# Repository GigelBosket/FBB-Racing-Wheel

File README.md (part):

# FBB-Racing-Wheel
Custom Racing Wheel with Force Feedback containing the wheelbase and steering wheel with the attachments to connect the 2 together. A custom PCB will be used to control the hoverboard motor and read it's position throw a rotary encoder connected to the motor with 2 gears. A Pico 2 is used in the wheelbase to receive data from the wheel(which also has a pico 2) throw SPI protocol. The pico 2 isn't used only for receiving data from the steering wheel, it could also get data from other devices like pedals, shifter, handrbrake and many more. The pico 2 supports up to 6 SPI/I2C connections and also sensors can directly be connected to it's GPIO pins.

The big difference between my racing wheel and others is that mine has direct data transfer throw the magnetic pins from steering wheel to wheelbase which goes in the pc. That means very small latency and no cable twisting all thanks to the magnetic pins (pogo pins) and the slipring. The downside that comes with this is the plastic parts for the high strain parts like the motor extension and the quick release all from plastic(3d printed) but it still should work fine.

I'm making the project so I could inspire others with my design as it's different than most I've seen. And also it's way cheaper than buying a new one with similar specs.

**Specs:**
 - up to 15nm of torque
 - fast response time of 1ms(1000hz)
 - wheel base is  L=20cm, W=20cm(at the corner, max dist) H=17cm.
 - steering wheel is 33cm
 - the 3d printed case for the steering wheel L=16.2cm, W=3.2cm, H=7.5.
 - 12 buttons
 - 5 encoders
 - 1 funcky switch(for easier customization of the car in games/other actions like camera fix position)
 - high precision encoder(for motor)

Wheel final version below

Wheel base

Close image from the steering wheel face

The back of the steering wheel 

Simple wiring scheme for the Pico 2 of the wheel base to the wires of the slip ring. The image also includes a simple connections from the pico 2 to some sensors if you want to directly connect any sensor to it.

Custom bldc motor driver PCB

PCB image of it's top copper layer

Steering wheel buttons/encoders will be connected to the pico 2 throw a matrix system in which each button is connected to column and row and the pico 2 will send a signal to each column and then wait for output from any of the rows and that's how it will find which buttons got pressed. This matrix system allows the usage of a high number of buttons without haveing a pin for each button. Also a diode will be used to prevent the current from flowing the opposite direction and causing ghosting. The order in which the buttons are connected doesn't matter so I won't include a photo of that. Also I won't add the file for schematic as it's a very simple schematic which isn't linked to other files and it's used to have and idea how the connections work for who doesn't already know(the wires can be connected to others pins and still work fine).Just don't forget to connect it to the pogo pins which then go to the Pico 2 in the wheel base which will process the data, don't forget to wire the pins accordingly for SPI protocol(example above). The pico 2 of the steering wheel is gonna be the slave while the pico in the base is gonna be the master. Slave awaits commands from master.

**Print tips**
So the parts used to connect the motor to the wheel should be printed with 95% infill, the oher parts should be printed with 15-30% infill as they won't have that much strain on them
I m gonna use ASA fillament as it is pretty strong and should do the job well.
Also if you are a total beginer you should download only the stl files as they are the only one needed to print the parts.

I used Raspberry Pi Pico extension in VS code which downloads the SDK for pico and other packages automaticly. If you want to use my code for Pico 2 just git clone my project then open the folder with the code you want to upload on your pico, in VS Code (after installing the extension) and just compile, select port of Pico 2 and upload.

Pico 2:

What you need to wire to the bldc motor driver PCB:

| BOM Total                                 |          |                | Price in us dollars |          |            |                                                                                                                                                                                                                                                                                                                                                                                                                                                                                                                                                                                                                                                                                  |
|-------------------------------------------|----------|----------------|---------------------|----------|------------|----------------------------------------------------------------------------------------------------------------------------------------------------------------------------------------------------------------------------------------------------------------------------------------------------------------------------------------------------------------------------------------------------------------------------------------------------------------------------------------------------------------------------------------------------------------------------------------------------------------------------------------------------------------------------------|
| Material/Product                          | Quantity | Price per Unit | SubTotal            | Shipping | TotalPrice | Link                                                                                                                                                                                                                                                                                                                                                                                                                                                                                                                                                                                                                                                                             |
| HoverBoard Motor                          | 1        | 20             | 20                  | 5        | 25         | Local Market(OLX.ro)                                                                                                                                                                                                                                                                                                                                                                                                                                                                                                                                                                                                                                                             |
| Pico 2                                    | 1        | 5.5            | 5.5                 | 6        | 11.5       | https://www.tme.eu/ro/cart/step/0/order/33780296                                                                                                                                                                                                                                                                                                                                                                                                                                                                                                                                                                                                                                 |
| SK16 support                              | 2        | 5.5            | 11                  | 5        | 16         | https://www.cnc-kit.ro/cumpara/sk16-suport-ax-16-mm-676                                                                                                                                                                                                                                                                                                                                                                                                                                                                                                                                                                                                                          |
| Rotary Encoder 38S6G5-B-G24N              | 1        | 11             | 11                  | 5        | 16         | https://www.aliexpress.com/item/1005006657099269.html?spm=a2g0o.detail.0.0.48bfnCCMnCCMPD&mp=1                                                                                                                                                                                                                                                                                                                                                                                                                                                                                                                                                                                   |
| MicroUsb convertor to Usb A               | 1        | 0.35           | 0.35                | 0        | 0.35       | https://www.aliexpress.com/item/1005005982662099.html?spm=a2g0o.detail.0.0.771aF986F986OE&mp=1                                                                                                                                                                                                                                                                                                                                                                                                                                                                                                                                                                                   |
| Usb C convertor to Usb A                  | 1        | 0.35           | 0.35                | 0        | 0.35       | https://www.aliexpress.com/item/1005005982662099.html?spm=a2g0o.detail.0.0.771aF986F986OE&mp=1                                                                                                                                                                                                                                                                                                                                                                                                                                                                                                                                                                                   |
| Aluminium Profile 20mm x 1m               | 1        | 8              | 8                   | 5        | 13         | https://www.automatic.ro/profiluri-de-aluminiu/510-profil-de-aluminiu-20x20-mm-canal-5-tip-item.html                                                                                                                                                                                                                                                                                                                                                                                                                                                                                                                                                                             |
| M4x10mm Screw                             | 48       | 0.04           | 1.92                | 0        | 1.92       | https://www.dedeman.ro/ro/surub-cu-cap-cilindric-cu-locas-hexagonal-otel-zincat-alb-din-912-8-8-sw-3-m4-x-10-mm/p/1033735                                                                                                                                                                                                                                                                                                                                                                                                                                                                                                                                                        |
| M4 nuts                                   | 48       | 0.012          | 0.576               | 0        | 0.58       | https://www.dedeman.ro/ro/piulita-hexagonala-din-otel-zincat-alb-din-934-m4/p/6000218                                                                                                                                                                                                                                                                                                                                                                                                                                                                                                                                                                                            |
| M5 screw(pack of 5)                       | 1        | 3.62           | 3.62                | 0        | 3.62       | https://www.dedeman.ro/ro/surub-cu-cap-cilindric-cu-locas-hexagonal-otel-zincat-alb-din-912-8-8-m5-x-30-mm-set-5-bucati/p/6014463                                                                                                                                                                                                                                                                                                                                                                                                                                                                                                                                                |
| M5 nuts                                   | 4        | 0.012          | 0.048               | 0        | 0.05       | https://www.dedeman.ro/ro/piulita-hexagonala-din-otel-zincat-alb-din-934-m5/p/6000211                                                                                                                                                                                                                                                                                                                                                                                                                                                                                                                                                                                            |
| Slip Ring                                 | 1        | 14             | 14                  | 0        | 14         | https://www.aliexpress.com/item/1005007469166149.html?spm=a2g0o.tesla.0.0.3dfdCxmRCxmRw3&afTraceInfo=1005007469166149__pc__c_ppc_item_bridge_pc_main__1392mx0__1764524967196                                                                                                                                                                                                                                                                                                                                                                                                                                                                                                     |
| 6 pin magnetic connector(male and female) | 1        | 2              | 2                   | 0        | 2          | https://www.aliexpress.com/item/1005010344872906.html?spm=a2g0o.productlist.0.0.23cd1f3eKvgHZs&mp=1                                                                                                                                                                                                                                                                                                                                                                                                                                                                                                                                                                              |
| Power Supply 24v 20A(80%efficiency)       | 1        | 39             | 39                  | 0        | 39         | https://www.aliexpress.com/item/33051556213.html?spm=a2g0o.cart.0.0.295838daYNvhOv&mp=1                                                                                                                                                                                                                                                                                                                                                                                                                                                                                                                                                                                          |
| 12AWG Red and Black cable                 | 1        | 7              | 7                   | 0        | 7          | https://www.aliexpress.com/item/1005008617874353.html?spm=a2g0o.productlist.main.1.17d020b4Rvij4e&aem_p4p_detail=2025122612534416560488550501840001829804&algo_pvid=f49deaba-5b28-4f73-bf14-0f9abc170d7e&pdp_ext_f=%7B%22order%22%3A%22690%22%2C%22eval%22%3A%221%22%2C%22fromPage%22%3A%22search%22%7D&utparam-url=scene%3Asearch%7Cquery_from%3A%7Cx_object_id%3A1005008617874353%7C_p_origin_prod%3A&search_p4p_id=2025122612534416560488550501840001829804_1                                                                                                                                                                                                                 |
| Steering Wheel                            | 1        | 59             | 59                  | 3        | 62         | https://www.aliexpress.com/item/1005005748732216.html?spm=a2g0o.detail.0.0.771aF986F986OE&mp=1                                                                                                                                                                                                                                                                                                                                                                                                                                                                                                                                                                                   |
| RKJXT1F42001                              | 1        | 3.66           | 3.66                | 0        | 3.66       | https://www.aliexpress.com/item/1005006287472896.html?spm=a2g0o.cart.0.0.295838daYNvhOv&mp=1                                                                                                                                                                                                                                                                                                                                                                                                                                                                                                                                                                                     |
| Push Button                               | 1        | 2.2            | 2.2                 | 0        | 2.2        | https://www.aliexpress.com/item/1005001700262900.html?spm=a2g0o.detail.pcDetailTopMoreOtherSeller.3.dedc2Nkd2Nkdsq&gps-id=pcDetailTopMoreOtherSeller&scm=1007.40050.354490.0&scm_id=1007.40050.354490.0&scm-url=1007.40050.354490.0&pvid=ea68574a-2666-4e59-a2fa-c057ce48ff6b&_t=gps-id:pcDetailTopMoreOtherSeller,scm-url:1007.40050.354490.0,pvid:ea68574a-2666-4e59-a2fa-c057ce48ff6b,tpp_buckets:668%232846%238108%231977&pdp_ext_f=%7B%22order%22%3A%2246%22%2C%22eval%22%3A%221%22%2C%22sceneId%22%3A%2230050%22%2C%22fromPage%22%3A%22recommend%22%7D&utparam-url=scene%3ApcDetailTopMoreOtherSeller%7Cquery_from%3A%7Cx_object_id%3A1005001700262900%7C_p_origin_prod%3A |
| Rotary encoders 15mm shaft(pack of 5)     | 1        | 3.7            | 3.7                 | 0        | 3.7        | https://www.aliexpress.com/item/32877104625.html?spm=a2g0o.productlist.main.1.48556bd7NRqWOd&aem_p4p_detail=202512260523295366502074963100001276967&algo_pvid=1431a988-9934-4868-8815-4e6e2980ab92&pdp_ext_f=%7B%22order%22%3A%229%22%2C%22eval%22%3A%221%22%2C%22fromPage%22%3A%22search%22%7D&utparam-url=scene%3Asearch%7Cquery_from%3A%7Cx_object_id%3A32877104625%7C_p_origin_prod%3A&search_p4p_id=202512260523295366502074963100001276967_1                                                                                                                                                                                                                               |
| Knob of rotary encoders (pack of 10(      | 1        | 1.4            | 1.4                 | 0        | 1.4        | https://www.aliexpress.com/item/1005006995837493.html?spm=a2g0o.productlist.main.16.58eba5a4rt7KPi&algo_pvid=26de8e72-05c5-4207-9564-9d77d845d36d&aem_p4p_detail=2025122605252814300115747411750001318343&pdp_ext_f=%7B%22order%22%3A%222%22%2C%22eval%22%3A%221%22%2C%22fromPage%22%3A%22search%22%7D&utparam-url=scene%3Asearch%7Cquery_from%3A%7Cx_object_id%3A1005006995837493%7C_p_origin_prod%3A&search_p4p_id=2025122605252814300115747411750001318343_6                                                                                                                                                                                                                  |
| M6 x60mm screw                            | 6        | 0.17           | 1.02                | 0        | 1.02       | https://www.dedeman.ro/ro/surub-cu-cap-hexagonal-filetat-complet-otel-zincat-alb-m6-x-60-mm/p/6000728                                                                                                                                                                                                                                                                                                                                                                                                                                                                                                                                                                            |
| M6 nuts                                   | 6        | 0.032          | 0.192               | 0        | 0.19       | https://www.dedeman.ro/ro/piulita-hexagonala-cu-autoblocare-din-otel-din-985-8-m6/p/6006481                                                                                                                                                                                                                                                                                                                                                                                                                                                                                                                                                                                      |
| M3 x16mm screw(pack of 20)                | 1        | 0.86           | 0.86                | 0        | 0.86       | https://www.dedeman.ro/ro/surub-cu-cap-bombat-amprenta-cruce-cu-piulita-easy-fix-otel-zincat-alb-m3-x-16-mm-set-20-bucati/p/6014509                                                                                                                                                                                                                                                                                                                                                                                                                                                                                                                                              |
| 1N4148                                    | 25       | 0.247          | 6.175               | 0        | 6.18       | https://www.tme.eu/ro/details/1n4148-dio/diode-universale-tht/diotec-semiconductor/1n4148/                                                                                                                                                                                                                                                                                                                                                                                                                                                                                                                                                                                       |
| 28AWG Black Cable                         | 2        | 0.5            | 1                   | 0.7      | 1.7        | https://www.aliexpress.com/item/1005008612186010.html?spm=a2g0o.cart.0.0.295838daYNvhOv&mp=1                                                                                                                                                                                                                                                                                                                                                                                                                                                                                                                                                                                     |
| 28AWG Red Cable                           | 2        | 0.5            | 1                   | 0        | 1          | https://www.aliexpress.com/item/1005008612186010.html?spm=a2g0o.cart.0.0.295838daYNvhOv&mp=1                                                                                                                                                                                                                                                                                                                                                                                                                                                                                                                                                                                     |
| PCB(min 5 Q)                              | 1        | 7              | 7                   | 3.12     | 10.12      |                                                                                                                                                                                                                                                                                                                                                                                                                                                                                                                                                                                                                                                                                  |
| PCB BOM(for 1 board)                      | 1        | 32             | 32                  | 9.52     | 41.52      |                                                                                                                                                                                                                                                                                                                                                                                                                                                                                                                                                                                                                                                                                  |
|                                           |          |                |                     |          |            |                                                                                                                                                                                                                                                                                                                                                                                                                                                                                                                                                                                                                                                                                  |
|                                           |          |                |                     |          |            |                                                                                                                                                                                                                                                                                                                                                                                                                                                                                                                                                                                                                                                                                  |
|                                           |          |                | 243.57              | 42.34    | 285.92     |                                                                                                                                                                                                                                                                                                                                                                                                                                                                                                                                              

**PCB BOM**
Price is around 23 euros for parts only on LCSC website + other fees.
| Designator                                                    | Footprint                                      | Quantity | Value                          | LCSC Part # |
|---------------------------------------------------------------|------------------------------------------------|----------|--------------------------------|-------------|
| 50W RESISTOR                                                  | DEGSON DG381-3.5-02P-14-00A(H)                 | 1        | DEGSON DG381-3.5-02P-14-00A(H) | C5272864    |
| C1, C12, C2, C23, C29, C30, C33, C39, C4, C40, C5, C6, C7, C8 | 402                                            | 14       | 100nF                          | C1525       |
| C10, C11, C3, C9                                              | 402                                            | 4        | 4.7uF                          | C23733      |
| C13, C20, C24, C25                                            | 805                                            | 4        | 22uF                           | C711104     |
| C14, C15, C16, C19, C27                                       | 603                                            | 5        | 1uF                            | C15849      |
| C17, C18                                                      | 402                                            | 2        | 15pF                           | C161530     |
| C21, C22, C31, C32, C34                                       | 805                                            | 5        | 10uF                           | C440198     |
| C26                                                           | 603                                            | 1        | 100nF                          | C1591       |
| C28                                                           | 603                                            | 1        | 47nF                           | C1622       |
| C35, C36, C37, C38                                            | CAP_EEEFK1H221P                                | 4        | 220uF                          | C72499      |
| D1                                                            | D_SMC                                          | 1        | SMCJ30A                        | C4154618    |
| D10                                                           | 402                                            | 1        | LED                            | C434446     |
| D2                                                            | D_SMA                                          | 1        | SS14                           | C2837270    |
| J1                                                            | USB_C_Receptacle_G-Switch_GT-USB-7051x         | 1        | USB_C_Receptacle_USB2.0_16P    | C2843970    |
| J3                                                            | JST_SH_BM05B-SRSS-TB_1x05-1MP_P1.00mm_Vertical | 1        | Encoder  Port                  | C160391     |
| J4                                                            | DORABO DB128V-5.08-5P-GN-S                     | 1        | DB128V-5.08-5P-GN-S            | C2927513    |
| L1                                                            | AOTA-B201610S3R3-101-T                         | 1        | 3.3uH                          | C42411119   |
| L2                                                            | VLS6045EX-4R7M-H                               | 1        | 4.7 uH                         | C360735     |
| L3                                                            | IND_ETQP4M220KVK                               | 1        | ETQP4M220KVK                   | C542324     |
| Q1, Q2, Q3, Q4, Q5, Q6                                        | TDSON-8-1                                      | 6        | CSD18532Q5B                    | C882766     |
| Q7                                                            | SOT-23                                         | 1        | IRLZ44N(UMW)                   | C42370423   |
| R1, R5, R6                                                    | 402                                            | 3        | 33                             | C25105      |
| R13, R14, R15, R4, R7                                         | 402                                            | 5        | 1k                             | C11702      |
| R16, R19, R29, R31                                            | 402                                            | 4        | 10k                            | C25744      |
| R18                                                           | 402                                            | 1        | 100k                           | C25741      |
| R2, R3                                                        | 402                                            | 2        | 5k1                            | C25905      |
| R20, R21, R22                                                 | 2512                                           | 3        | 5M1                            | C419720     |
| R30                                                           | 402                                            | 1        | 31k6                           | C11463      |
| R8, R9                                                        | 402                                            | 2        | 27                             | C278580     |
| S1                                                            | SW_TL3365AF180QG                               | 1        | TL3365AF180QG                  | C2886926    |
| U1                                                            | QFN-48-1EP_7x7mm_P0.5mm_EP5.3x5.3mm            | 1        | DRV8323RSRGZR                  | C545497     |
| U2                                                            | QFN-60-1EP_7x7mm_P0.4mm_EP3.4x3.4mm            | 1        | RP2354A                        | C41378174   |
| U3                                                            | TSOT-23-6                                      | 1        | AP63203WU                      | C780769     |
| Y2                                                            | XTAL_ABM8-272-T3                               | 1        | ABM8-272-T3                    | C20625731   |

The next 2 BOMS are an aproximation for how much for just one of them. It is not 100% accurate

|Wheelbase                                |        |              |         |         |Price in US dollars|                                                                                                                                                                                                                                                                                                                                                                                                                                                            |
|-----------------------------------------|--------|--------------|---------|---------|-------------------|----------------------------------------------------------------------------------------------------------------------------------------------------------------------------------------------------------------------------------------------------------------------------------------------------------------------------------------------------------------------------------------------------------------------------------------------------------------|
|Material/Product                         |Quantity|Price per Unit|SubTotal |Shipping |TotalPrice         |Link                                                                                                                                                                                                                                                                                                                                                                                                                                                            |
|HoverBoard Motor                         |1       |20            |20       |5        |25                 |Local Market(OLX.ro)                                                                                                                                                                                                                                                                                                                                                                                                                                                                                                                                                                                                                                                   |
|Pico 2                                   |1       |5.5           |5.5      |6        |11.5               |[link](https://www.tme.eu/ro/cart/step/0/order/33780296)                                                                                                                                                                                                                                                                                                                                                                                                                |
|SK16 support                             |2       |5.5           |11       |5        |16                 |[link](https://www.cnc-kit.ro/cumpara/sk16-suport-ax-16-mm-676)                                                                                                                                                                                                                                                                                                                                                                                                         |
|Rotary Encoder 38S6G5-B-G24N             |1       |11            |11       |5        |16                 |[link](https://www.aliexpress.com/item/1005006657099269.html?spm=a2g0o.detail.0.0.48bfnCCMnCCMPD&mp=1)                                                                                                                                                                                                                                                                                                                                                                  |
|MicroUsb convertor to Usb A              |1       |0.35          |0.35     |0        |0.35               |[link](https://www.aliexpress.com/item/1005005982662099.html?spm=a2g0o.detail.0.0.771aF986F986OE&mp=1)                                                                                                                                                                                                                                                                                                                                                                  |
|Usb C convertor to Usb A                 |1       |0.35          |0.35     |0        |0.35               |[link](https://www.aliexpress.com/item/1005005982662099.html?spm=a2g0o.detail.0.0.771aF986F986OE&mp=1)                                                                                                                                                                                                                                                                                                                                                                  |
|Aluminium Profile 20mm x 1m              |1       |8             |8        |5        |13                 |[link](https://www.automatic.ro/profiluri-de-aluminiu/510-profil-de-aluminiu-20x20-mm-canal-5-tip-item.html)                                                                                                                                                                                                                                                                                                                                                            |
|M4x10mm Screw                            |48      |0.04          |1.92     |0        |1.92               |[link](https://www.dedeman.ro/ro/surub-cu-cap-cilindric-cu-locas-hexagonal-otel-zincat-alb-din-912-8-8-sw-3-m4-x-10-mm/p/1033735)                                                                                                                                                                                                                                                                                                                                       |
|M4 nuts                                  |48      |0.012         |0.576    |0        |0.58               |[link](https://www.dedeman.ro/ro/piulita-hexagonala-din-otel-zincat-alb-din-934-m4/p/6000218)                                                                                                                                                                                                                                                                                                                                                                           |                                                                                                                                                                                                                                                                                                                                                                                                                                                               |
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
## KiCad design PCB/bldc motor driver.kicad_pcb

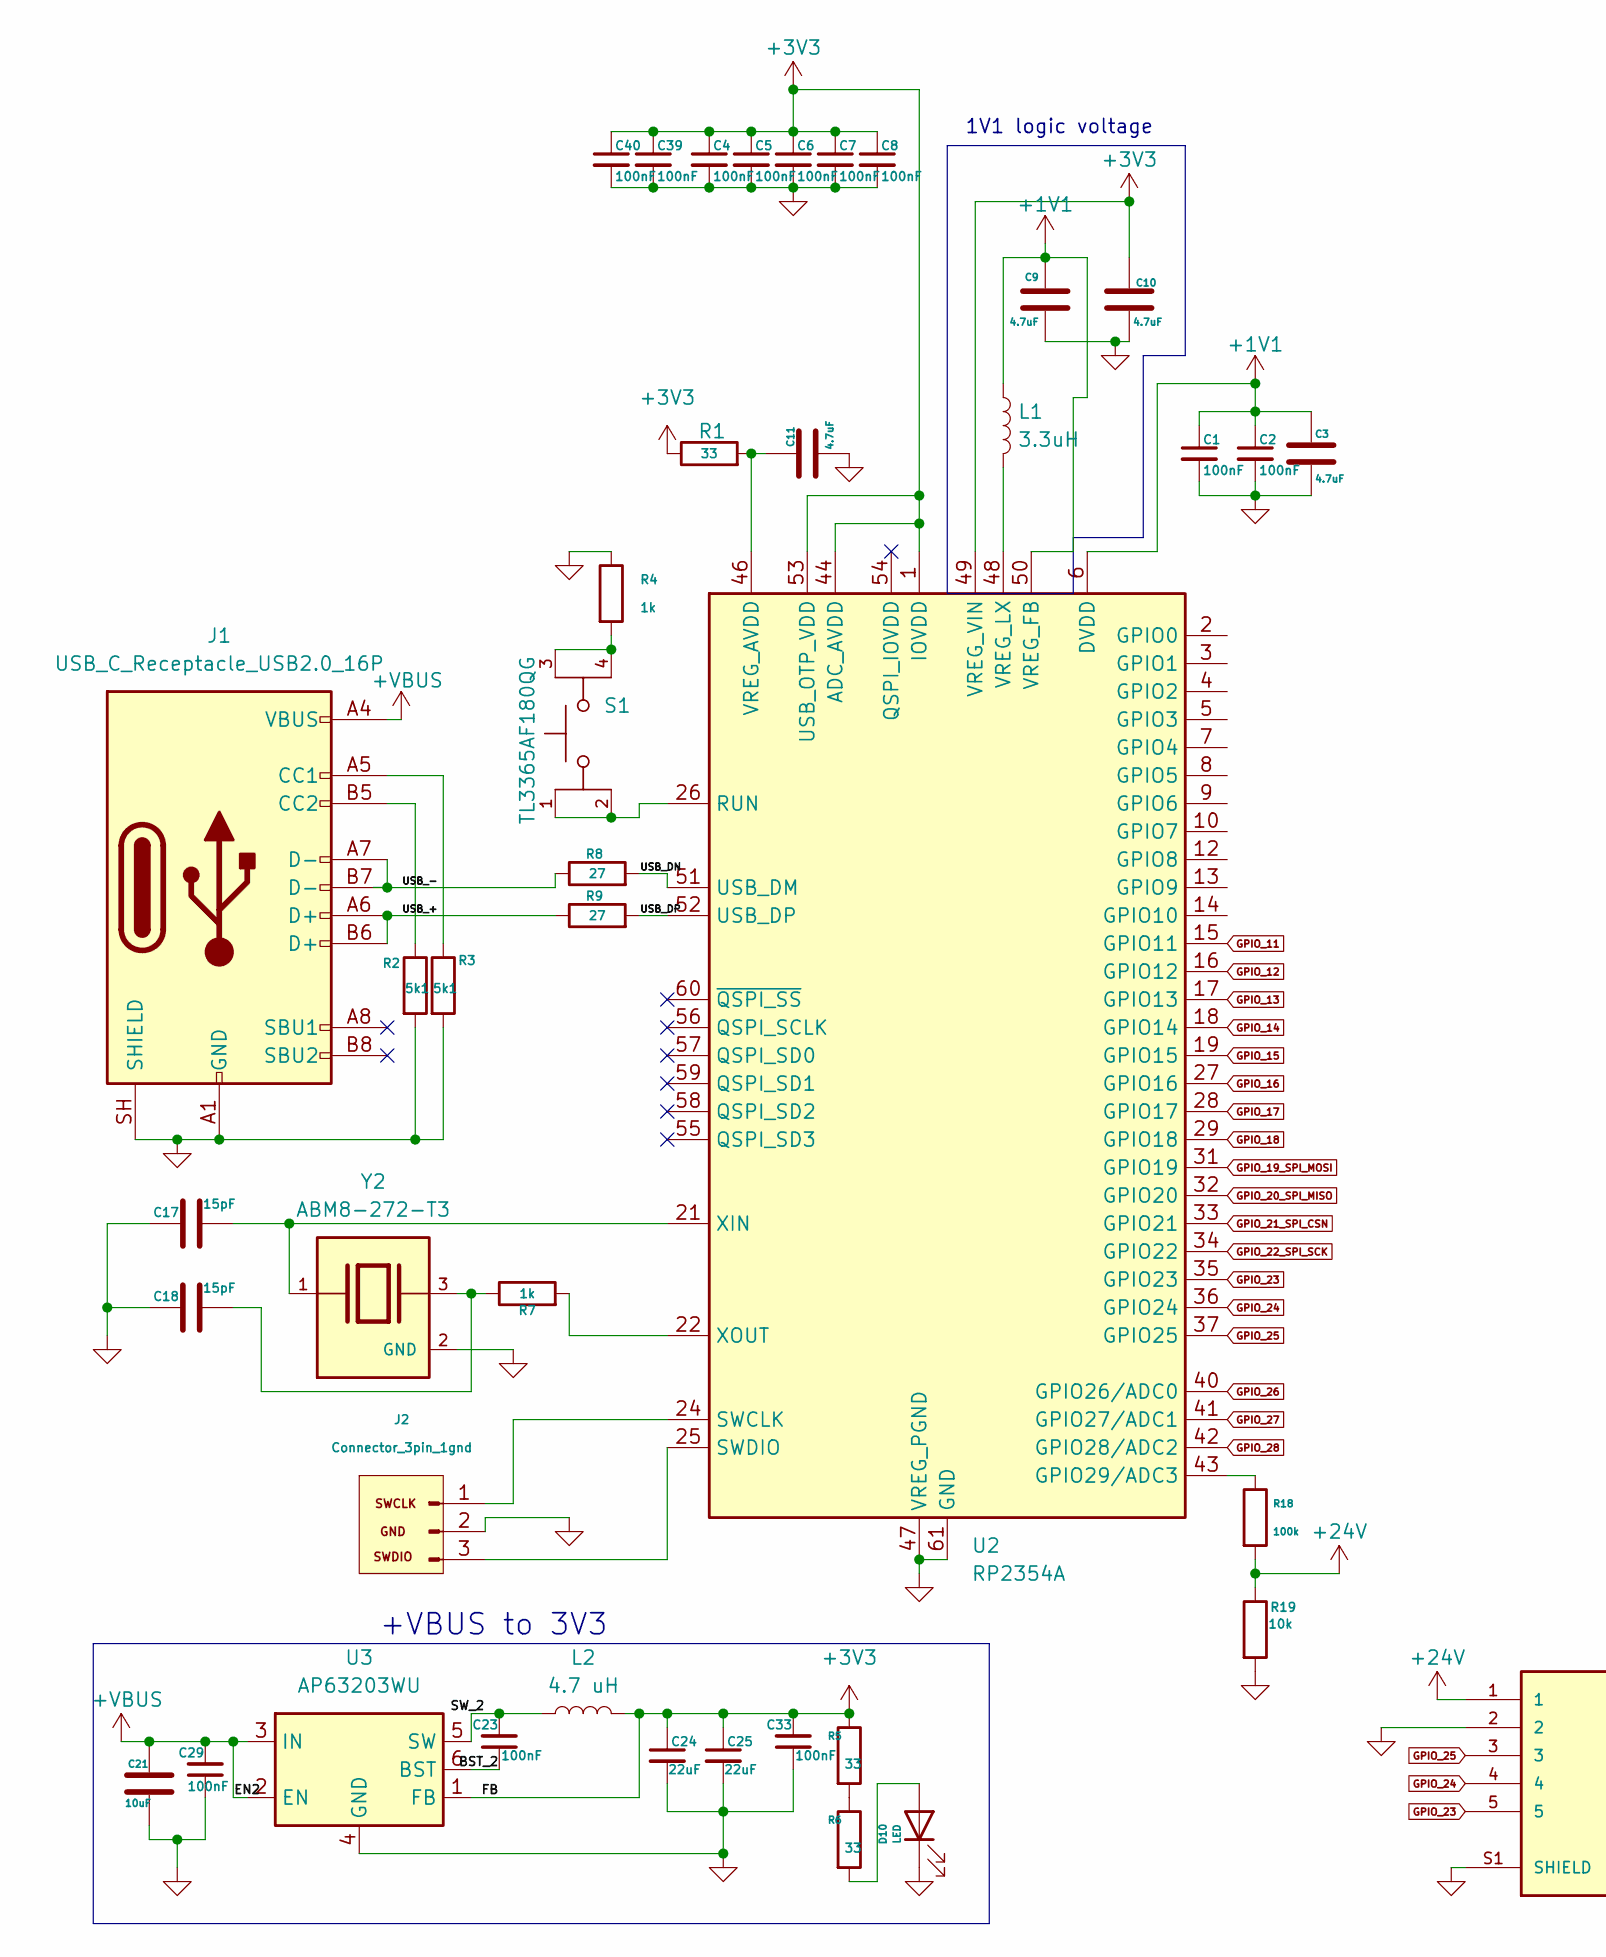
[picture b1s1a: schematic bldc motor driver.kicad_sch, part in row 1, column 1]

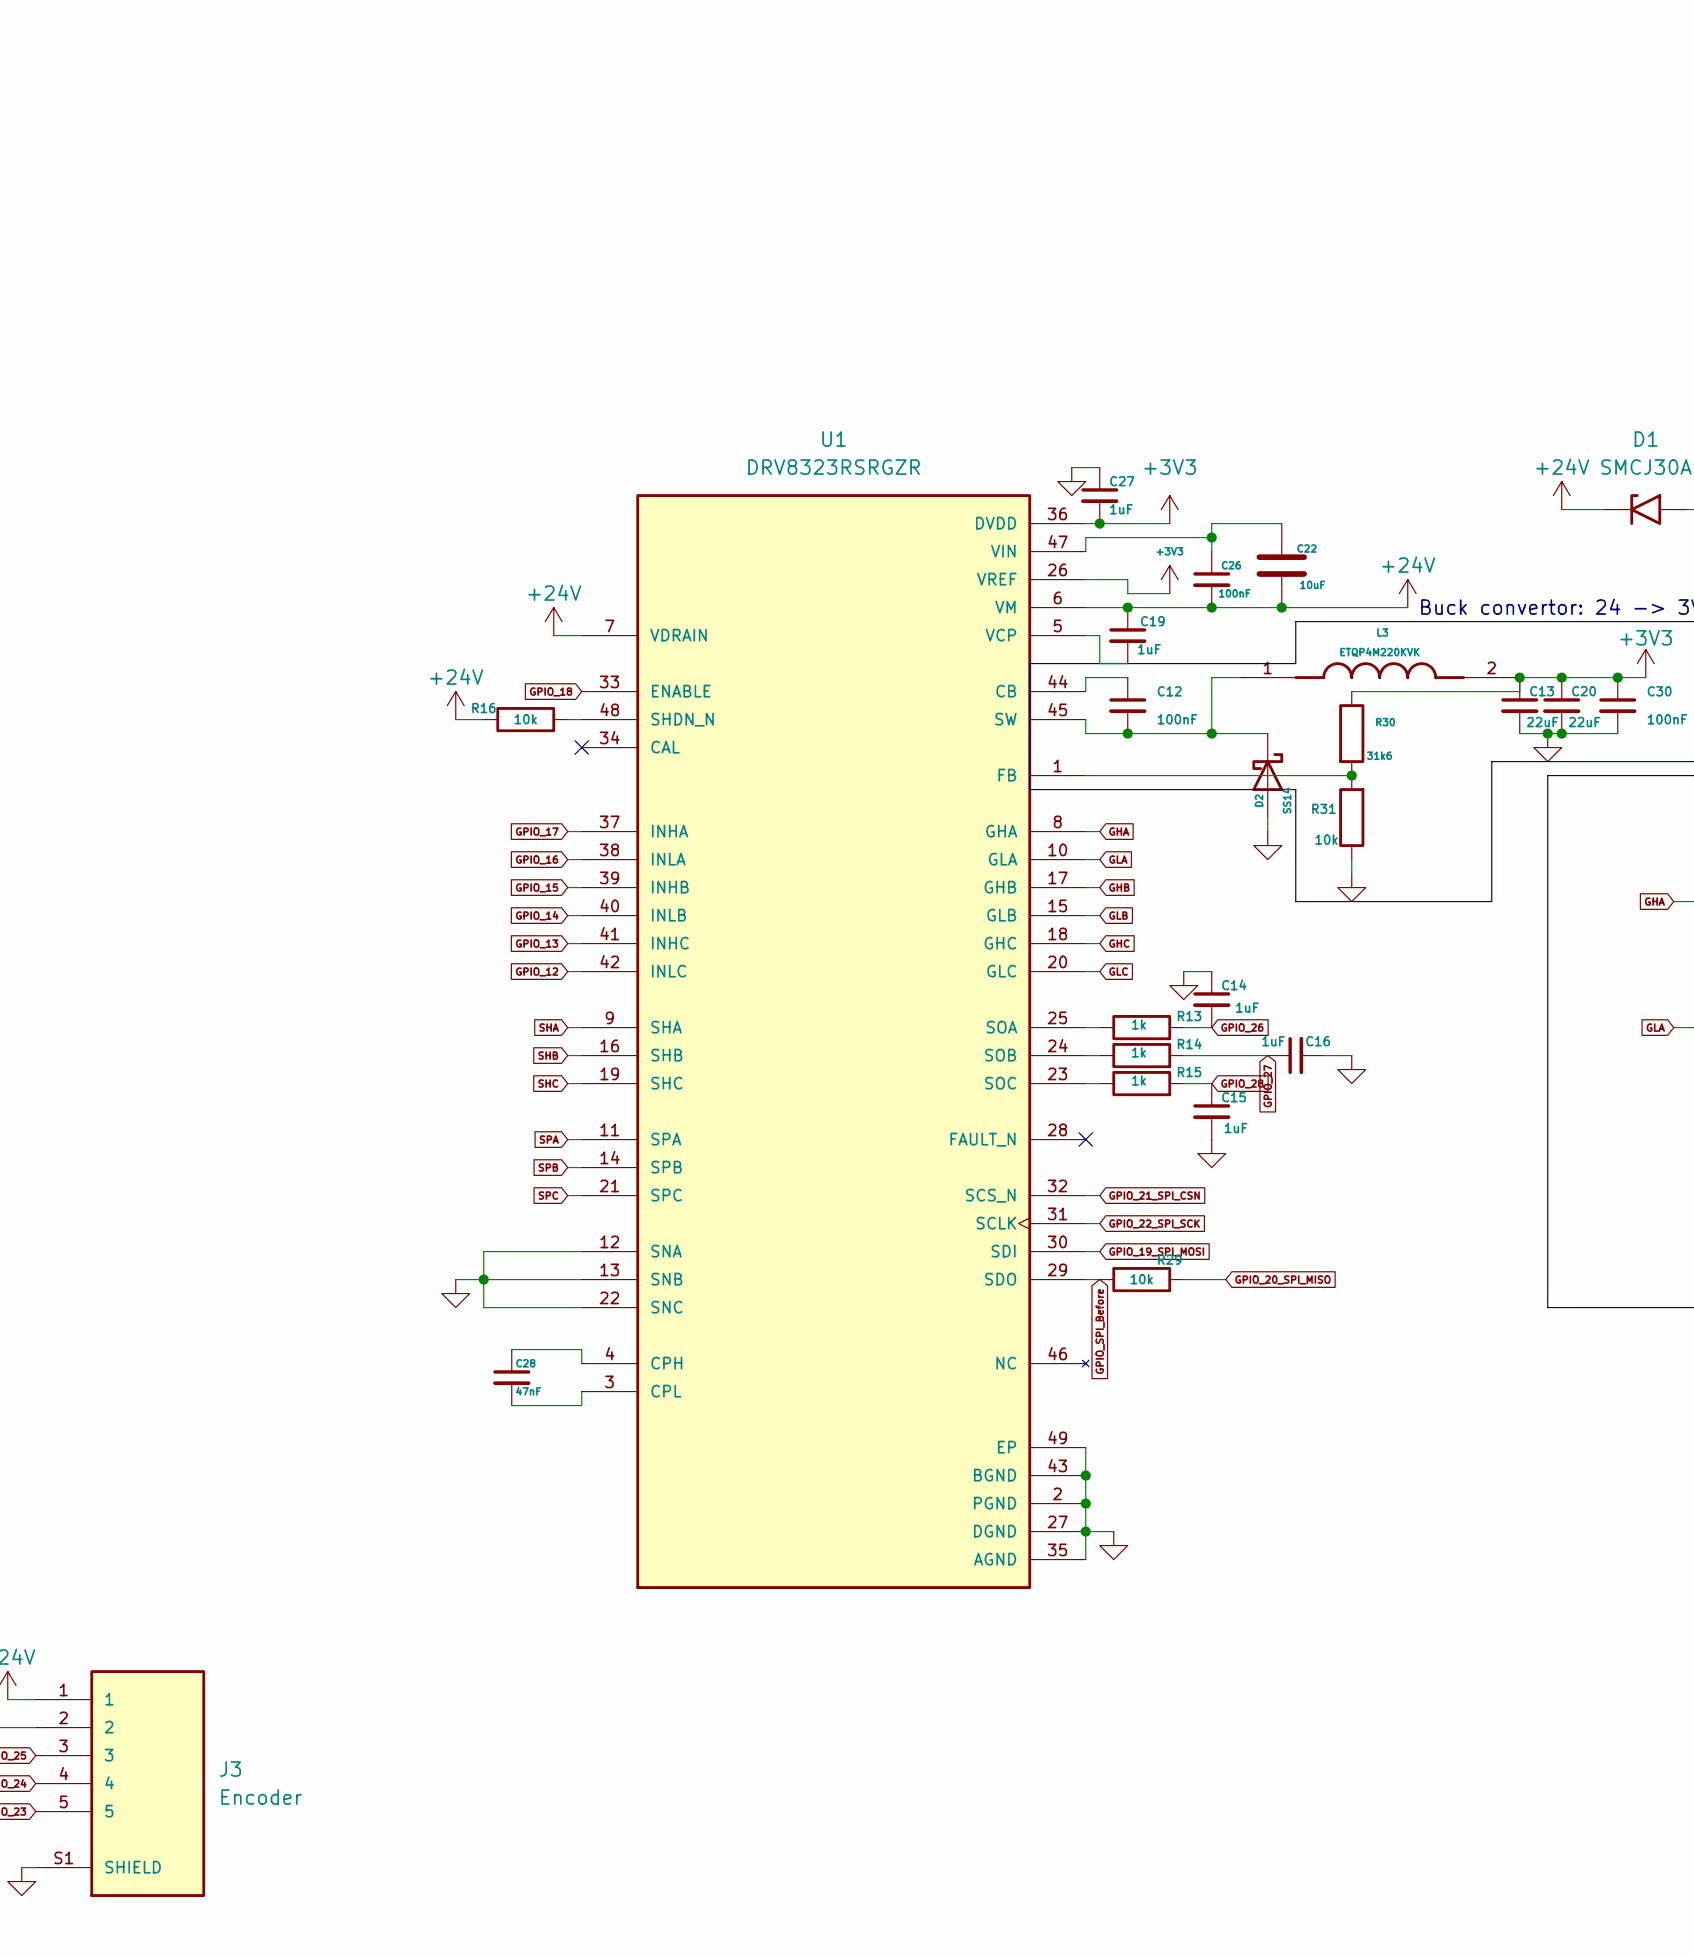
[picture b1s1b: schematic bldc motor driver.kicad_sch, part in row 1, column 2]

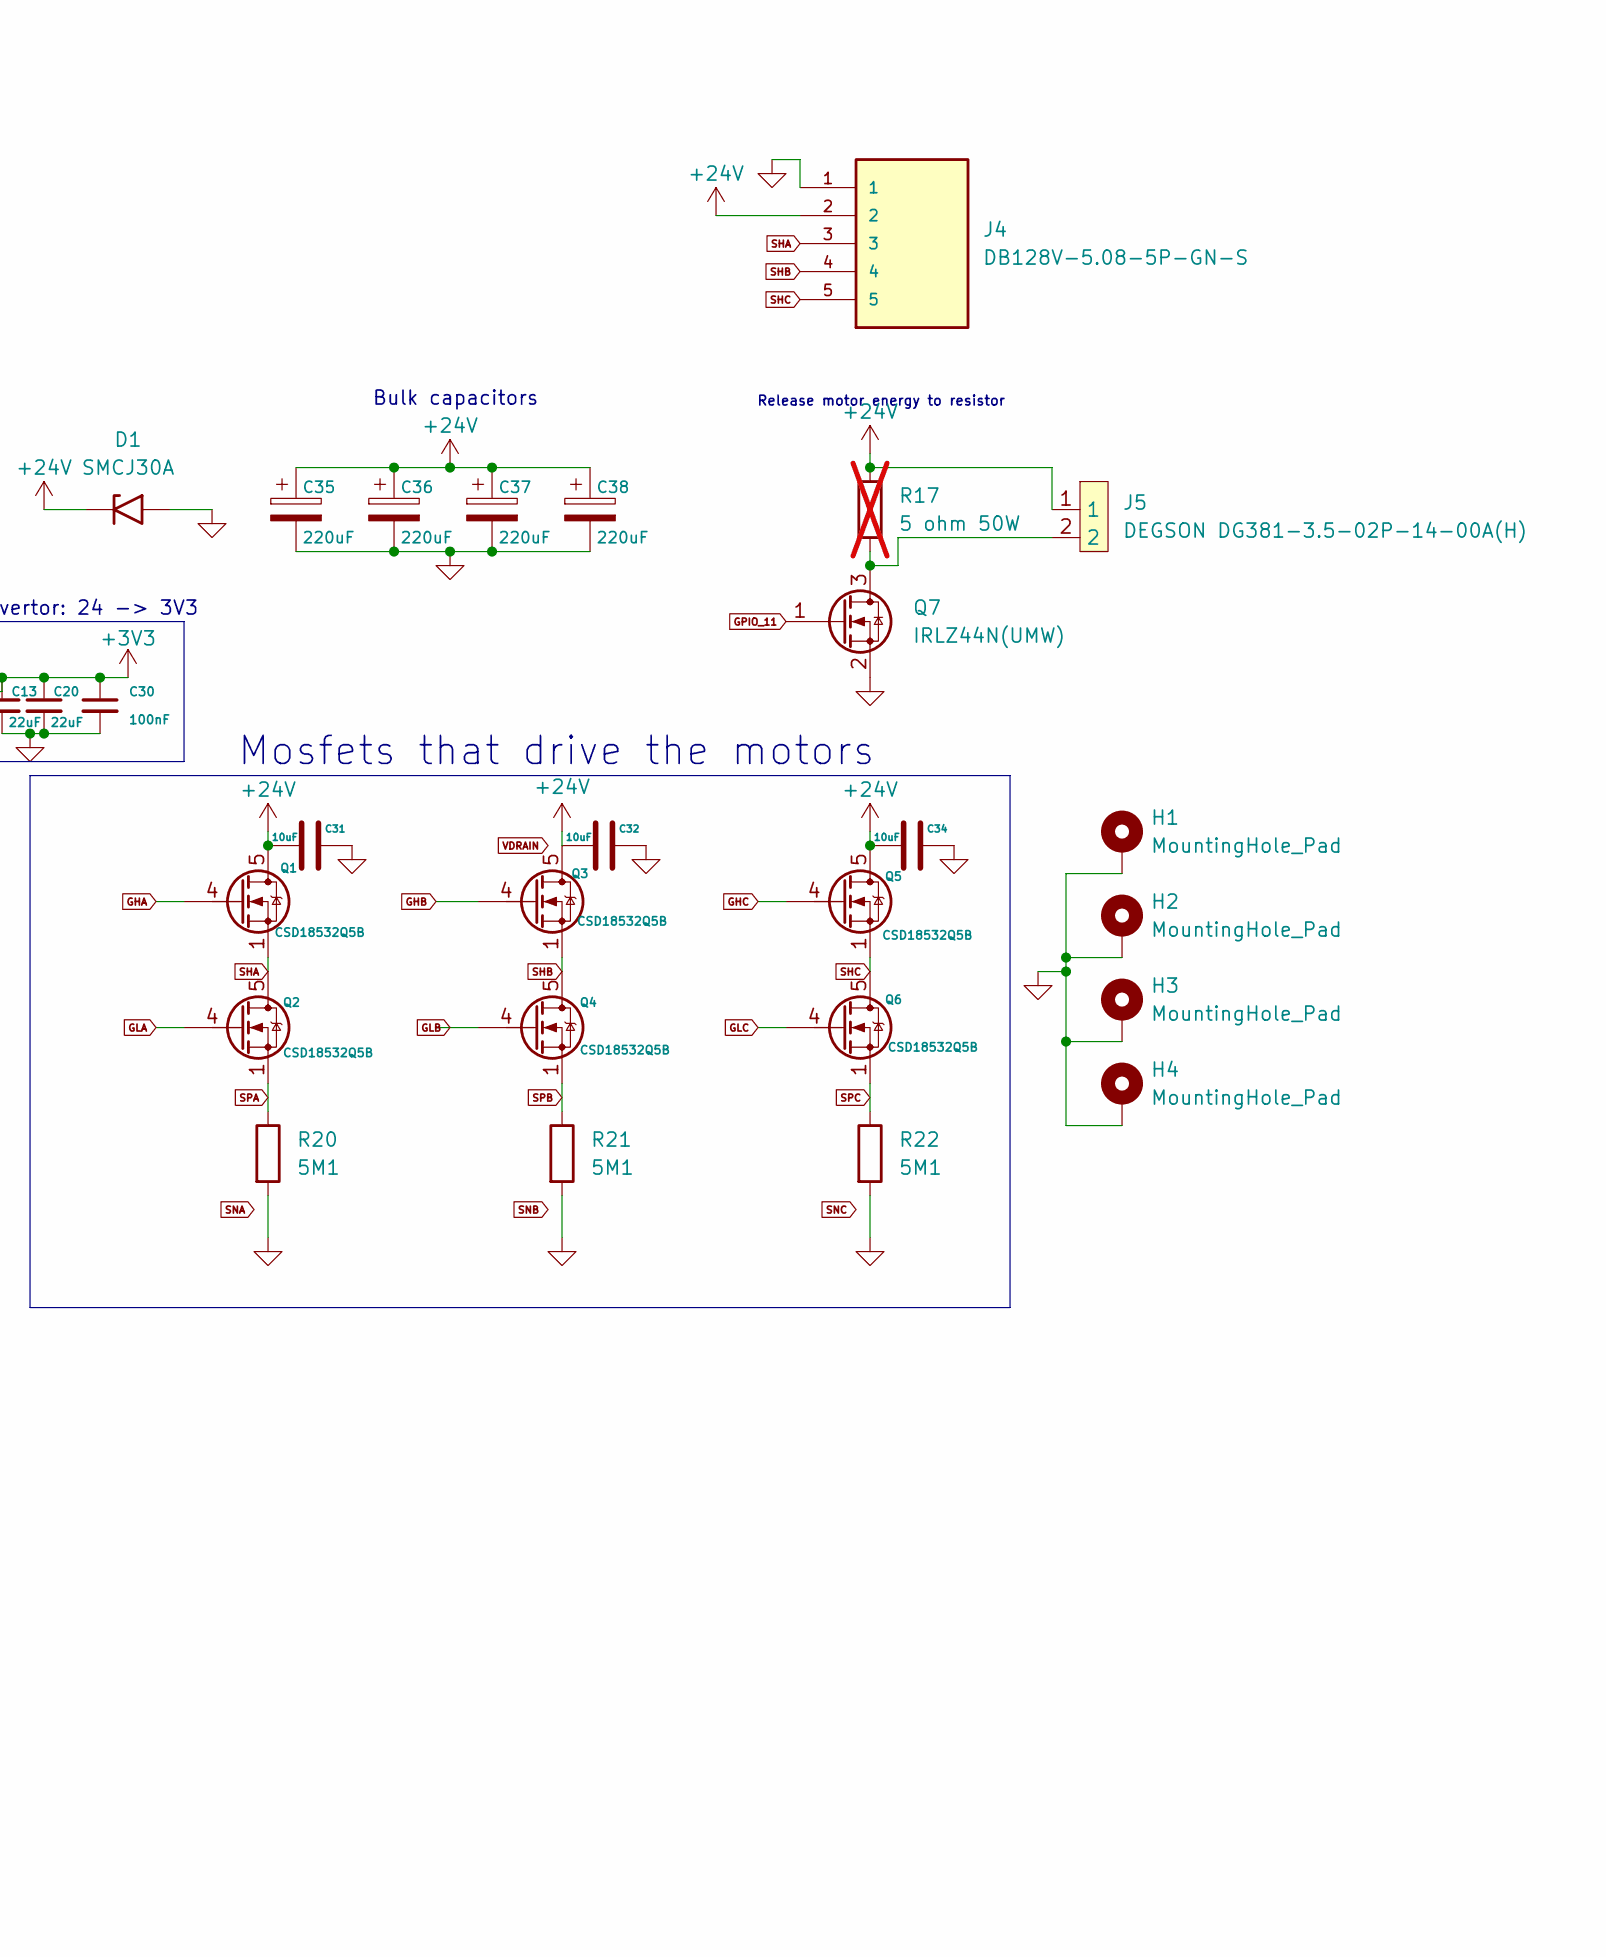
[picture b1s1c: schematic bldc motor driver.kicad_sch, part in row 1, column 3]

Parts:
C1, C2, C4, C5, C6, C7, C8, C12, C30, C39, C40: 100nF; C_0402_1005Metric; MPN CL05B104KO5NNNC; LCSC C1525
C3, C9, C10, C11: 4.7uF; C_0402_1005Metric; MPN CL05A475MP5NRNC; LCSC C23733
C13, C20, C24, C25: 22uF; C_0805_2012Metric; MPN GXT21BR61C226ME13L; LCSC C711104
C14, C15, C16, C19, C27: 1uF; C_0603_1608Metric; MPN CL10A105KB8NNNC; LCSC C15849
C17, C18: 15pF; C_0402_1005Metric smaller silk; MPN GRM1555C1H150FA01D; LCSC C161530
C21, C22, C31, C32, C34: 10uF; C_0805_2012Metric; MPN GRM21BR61H106KE43L; LCSC C440198
C23, C29, C33: 100nF; C_0402_1005Metric smaller silk; MPN CL05B104KO5NNNC; LCSC C1525
C26: 100nF; C_0603_1608Metric; MPN CL10B104KB8NNNC; LCSC C1591
C28: 47nF; C_0603_1608Metric; MPN CL10B473KB8NNNC; LCSC C1622
C35, C36, C37, C38: 220uF; CAP_EEEFK1H221P; MPN RVT1H221M1010; LCSC C72499
D1: SMCJ30A; D_SMC; MPN SMCJ30A; LCSC C4154618
D2: SS14; D_SMA; MPN SS14; LCSC C2837270
D10: LED; LED_0402_1005Metric; MPN SZYY0402G; LCSC C434446
H1, H2, H3, H4: MountingHole_Pad; MountingHole_2.2mm_M2_DIN965_Pad
J1: USB_C_Receptacle_USB2.0_16P; USB_C_Receptacle_G-Switch_GT-USB-7051x
J2: Connector_3pin_1gnd; 3 pin connector middle ground
J3: Encoder; JST_SH_BM05B-SRSS-TB_1x05-1MP_P1.00mm_Vertical; PARTREV N/A
J4: DB128V-5.08-5P-GN-S; DORABO DB128V-5.08-5P-GN-S; MPN DB128V-5.08-5P-GN-S; LCSC C2927513
J5: DEGSON DG381-3.5-02P-14-00A(H); MPN DG381-3.5-02P-14-00A(H); LCSC C5272864
L1: 3.3uH; AOTA-B201610S3R3-101-T; MPN AOTA-B201610S3R3-101-T; LCSC C42411119
L2: 4.7 uH; VLS6045EX-4R7M-H; MPN VLS6045EX-4R7M-H; LCSC C360735
L3: ETQP4M220KVK; IND_ETQP4M220KVK; PARTREV 1-Feb-20; LCSC C542324
Q1, Q2, Q3, Q4, Q5, Q6: CSD18532Q5B; TDSON-8-1
Q7: IRLZ44N(UMW); SOT-23; MPN IRLZ44N(UMW); LCSC C42370423
R1, R5, R6: 33; R_0402_1005Metric; MPN 0402WGF330JTCE; LCSC C25105
R2, R3: 5k1; R_0402_1005Metric smaller silkscreen; MPN 0402WGF5101TCE; LCSC C25905
R4, R13, R14, R15: 1k; R_0402_1005Metric; MPN 0402WGF1001TCE; LCSC C11702
R7: 1k; R_0402_1005Metric smaller silkscreen; MPN 0402WGF1001TCE; LCSC C11702
R8, R9: 27; R_0402_1005Metric; MPN ERJ-2GEJ270X; LCSC C278580
R16, R19, R29, R31: 10k; R_0402_1005Metric smaller silkscreen; MPN 0402WGF1002TCE; LCSC C25744
R17: 5 ohm 50W; MPN HoRX-50W-5R-5%; LCSC C2923747; not fitted
R18: 100k; R_0402_1005Metric; MPN 0402WGF1003TCE; LCSC C25741
R20, R21, R22: 5M1; R_2512_6332Metric; MPN 25121WJ0515T4E; LCSC C419720
R30: 31k6; R_0402_1005Metric; MPN 0402WGF3162TCE; LCSC C11463
S1: TL3365AF180QG; SW_TL3365AF180QG; PARTREV A
U1: DRV8323RSRGZR; QFN-48-1EP_7x7mm_P0.5mm_EP5.3x5.3mm; PARTREV C
U2: RP2354A; QFN-60-1EP_7x7mm_P0.4mm_EP3.4x3.4mm
U3: AP63203WU; TSOT-23-6; MPN AP63203WU-7; LCSC C780769
Y2: ABM8-272-T3; XTAL_ABM8-272-T3; PARTREV 07-29-20; LCSC C20625731

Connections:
+1V1: C1.1, C2.1, C3.1, C9.1, L1.1, U2.6 (DVDD), U2.23 (DVDD), U2.39 (DVDD), U2.50 (VREG_FB)
+3V3: C4.1, C5.1, C6.1, C7.1, C8.1, C10.1, C13.1, C20.1, C24.1, C25.1, C27.2, C30.1, C33.2, C39.1, C40.1, L2.2, L3.2, R1.1, R5.1, R30.1, U1.26 (VREF), U1.36 (DVDD), U2.1 (IOVDD), U2.11 (IOVDD), U2.20 (IOVDD), U2.30 (IOVDD), U2.38 (IOVDD), U2.44 (ADC_AVDD), U2.45 (IOVDD), U2.49 (VREG_VIN), U2.53 (USB_OTP_VDD), U3.1 (FB)
+24V: C19.1, C22.2, C26.2, C31.1, C32.1, C34.1, C35.1, C36.1, C37.1, C38.1, D1.1 (A1), J3.1, J4.2, J5.1, Q1.5 (D), Q3.5 (D), Q5.5 (D), R16.1, R17.1, R18.2, R19.1, U1.6 (VM), U1.7 (VDRAIN); also elsewhere on the board
+VBUS: C21.1, C29.2, J1.A4 (VBUS), J1.A9 (VBUS), J1.B4 (VBUS), J1.B9 (VBUS), U3.2 (EN), U3.3 (IN)
/BST_2: C23.1, U3.6 (BST)
/SW_2: C23.2, L2.1, U3.5 (SW)
/USB_+: J1.A6 (D+), J1.B6 (D+), R9.1
/USB_-: J1.A7 (D-), J1.B7 (D-), R8.1
/USB_DN: R8.2, U2.51 (USB_DM)
/USB_DP: R9.2, U2.52 (USB_DP)
GHA: Q1.4 (G), U1.8 (GHA)
GHB: Q3.4 (G), U1.17 (GHB)
GHC: Q5.4 (G), U1.18 (GHC)
GLA: Q2.4 (G), U1.10 (GLA)
GLB: Q4.4 (G), U1.15 (GLB)
GLC: Q6.4 (G), U1.20 (GLC)
GND: C1.2, C2.2, C3.2, C4.2, C5.2, C6.2, C7.2, C8.2, C9.2, C10.2, C11.2, C13.2, C14.1, C15.2, C16.2, C17.1, C18.1, C20.2, C21.2, C24.2, C25.2, C27.1, C29.1, C30.2, C31.2, C32.2, C33.1, C34.2, C35.2, C36.2, C37.2, C38.2, C39.2, C40.2, D1.2 (A2), D2.2 (A), D10.1 (K), H1.1 (1_1), H2.1 (1_1), H3.1 (1_1), H4.1 (1_1), J1.A1 (GND), J1.A12 (GND), J1.B1 (GND), J1.B12 (GND), J1.SH (SHIELD), J2.2 (GND), J3.2, J3.S1 (SHIELD), J3.S2 (SHIELD), J4.1, Q7.2 (S), R2.2, R3.2, R4.1, R19.2, R20.2, R21.2, R22.2, R31.1, U1.2 (PGND), U1.12 (SNA), U1.13 (SNB), U1.22 (SNC), U1.27 (DGND), U1.35 (AGND), U1.43 (BGND), U1.49 (EP), U2.47 (VREG_PGND), U2.61 (GND), U3.4 (GND), Y2.2 (GND), Y2.4 (GND)
GPIO_11: Q7.1 (G), U2.15 (GPIO11)
GPIO_12: U1.42 (INLC), U2.16 (GPIO12)
GPIO_13: U1.41 (INHC), U2.17 (GPIO13)
GPIO_14: U1.40 (INLB), U2.18 (GPIO14)
GPIO_15: U1.39 (INHB), U2.19 (GPIO15)
GPIO_16: U1.38 (INLA), U2.27 (GPIO16)
GPIO_17: U1.37 (INHA), U2.28 (GPIO17)
GPIO_18: U1.33 (ENABLE), U2.29 (GPIO18)
GPIO_19_SPI_MOSI: U1.30 (SDI), U2.31 (GPIO19)
GPIO_20_SPI_MISO: R29.2, U2.32 (GPIO20)
GPIO_21_SPI_CSN: U1.32 (SCS_N), U2.33 (GPIO21)
GPIO_22_SPI_SCK: U1.31 (SCLK), U2.34 (GPIO22)
GPIO_23: J3.5, U2.35 (GPIO23)
GPIO_24: J3.4, U2.36 (GPIO24)
GPIO_25: J3.3, U2.37 (GPIO25)
GPIO_26: C14.2, R13.2, U2.40 (GPIO26/ADC0)
GPIO_27: C16.1, R14.2, U2.41 (GPIO27/ADC1)
GPIO_28: C15.1, R15.2, U2.42 (GPIO28/ADC2)
GPIO_SPI_Before: R29.1, U1.29 (SDO)
unnamed: C18.2, R7.1, Y2.3
unnamed: C12.2, D2.1 (K), L3.1, U1.45 (SW)
unnamed: D10.2 (A), R6.2
unnamed: J1.A5 (CC1), R3.1
unnamed: J1.B5 (CC2), R2.1
unnamed: J2.1 (SWCLK), U2.24 (SWCLK)
unnamed: J2.3 (SWDIO), U2.25 (SWDIO)
unnamed 43: J5.2, Q7.3 (D), R17.2; also elsewhere on the board
unnamed: R4.2, S1.3, S1.4
unnamed: R5.2, R6.1
unnamed: C12.1, U1.44 (CB)
unnamed: C28.1, U1.4 (CPH)
unnamed: C28.2, U1.3 (CPL)
unnamed: R30.2, R31.2, U1.1 (FB)
unnamed: R16.2, U1.48 (SHDN_N)
unnamed: R13.1, U1.25 (SOA)
unnamed: R14.1, U1.24 (SOB)
unnamed: R15.1, U1.23 (SOC)
unnamed: C19.2, U1.5 (VCP)
unnamed: C22.1, C26.1, U1.47 (VIN)
unnamed: R18.1, U2.43 (GPIO29/ADC3)
unnamed: S1.1, S1.2, U2.26 (RUN)
unnamed: C11.1, R1.2, U2.46 (VREG_AVDD)
unnamed: L1.2, U2.48 (VREG_LX)
unnamed: C17.2, U2.21 (XIN), Y2.1
unnamed: R7.2, U2.22 (XOUT)
SHA: J4.3, Q1.1 (S), Q1.2 (S), Q1.3 (S), Q2.5 (D), U1.9 (SHA)
SHB: J4.4, Q3.1 (S), Q3.2 (S), Q3.3 (S), Q4.5 (D), U1.16 (SHB)
SHC: J4.5, Q5.1 (S), Q5.2 (S), Q5.3 (S), Q6.5 (D), U1.19 (SHC)
SPA: Q2.1 (S), Q2.2 (S), Q2.3 (S), R20.1, U1.11 (SPA)
SPB: Q4.1 (S), Q4.2 (S), Q4.3 (S), R21.1, U1.14 (SPB)
SPC: Q6.1 (S), Q6.2 (S), Q6.3 (S), R22.1, U1.21 (SPC)

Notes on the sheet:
Bulk capacitors
+VBUS to 3V3
Release motor energy to resistor
Mosfets that drive the motors
Buck convertor: 24 -> 3V3
1V1 logic voltage

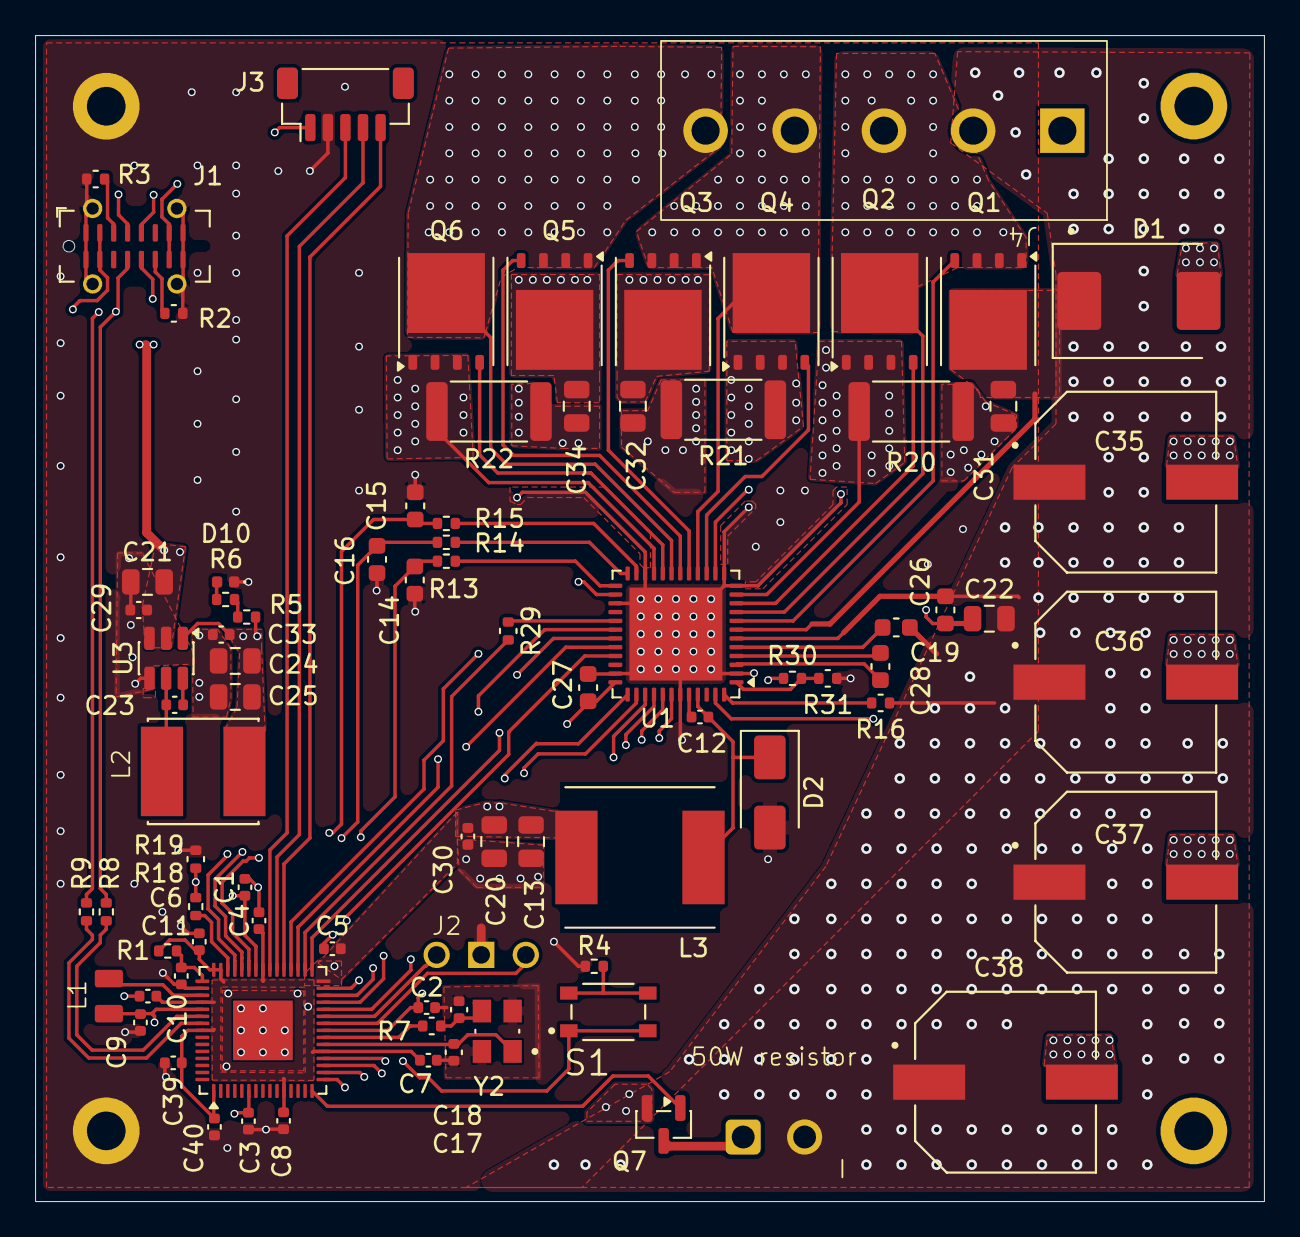
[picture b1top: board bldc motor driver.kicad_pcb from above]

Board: 4 copper layers, 70.0 x 66.4 mm, 88 parts (0 on the bottom side), 68 nets.

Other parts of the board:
50W resistor: DEGSON DG381-3.5-02P-14-00A(H)

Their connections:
+24V: 50W resistor.1; also elsewhere on the board
unnamed 43: 50W resistor.2; also elsewhere on the board

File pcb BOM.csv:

Designator,Footprint,Quantity,Value,LCSC Part #
50W RESISTOR,DEGSON DG381-3.5-02P-14-00A(H),1,DEGSON DG381-3.5-02P-14-00A(H),C5272864
"C1, C12, C2, C23, C29, C30, C33, C39, C4, C40, C5, C6, C7, C8",402,14,100nF,C1525
"C10, C11, C3, C9",402,4,4.7uF,C23733
"C13, C20, C24, C25",805,4,22uF,C711104
"C14, C15, C16, C19, C27",603,5,1uF,C15849
"C17, C18",402,2,15pF,C161530
"C21, C22, C31, C32, C34",805,5,10uF,C440198
C26,603,1,100nF,C1591
C28,603,1,47nF,C1622
"C35, C36, C37, C38",CAP_EEEFK1H221P,4,220uF,C72499
D1,D_SMC,1,SMCJ30A,C4154618
D10,402,1,LED,C434446
D2,D_SMA,1,SS14,C2837270
J1,USB_C_Receptacle_G-Switch_GT-USB-7051x,1,USB_C_Receptacle_USB2.0_16P,C2843970
J3,JST_SH_BM05B-SRSS-TB_1x05-1MP_P1.00mm_Vertical,1,Encoder,
J4,DORABO DB128V-5.08-5P-GN-S,1,DB128V-5.08-5P-GN-S,C2927513
L1,AOTA-B201610S3R3-101-T,1,3.3uH,C42411119
L2,VLS6045EX-4R7M-H,1,4.7 uH,C360735
L3,IND_ETQP4M220KVK,1,ETQP4M220KVK,C542324
"Q1, Q2, Q3, Q4, Q5, Q6",TDSON-8-1,6,CSD18532Q5B,
Q7,SOT-23,1,IRLZ44N(UMW),C42370423
"R1, R5, R6",402,3,33,C25105
"R13, R14, R15, R4, R7",402,5,1k,C11702
"R16, R19, R29, R31",402,4,10k,C25744
R18,402,1,100k,C25741
"R2, R3",402,2,5k1,C25905
"R20, R21, R22",2512,3,5M1,C419720
R30,402,1,31k6,C11463
"R8, R9",402,2,27,C278580
S1,SW_TL3365AF180QG,1,TL3365AF180QG,C2886926
U1,QFN-48-1EP_7x7mm_P0.5mm_EP5.3x5.3mm,1,DRV8323RSRGZR,
U2,QFN-60-1EP_7x7mm_P0.4mm_EP3.4x3.4mm,1,RP2354A,
U3,TSOT-23-6,1,AP63203WU,C780769
Y2,XTAL_ABM8-272-T3,1,ABM8-272-T3,C20625731

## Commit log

2025-12-26 Change license to CC BY-NC-SA 4.0
    Change license to CC BY-NC-SA 4.0
2025-12-26 added images and BOM
2025-12-26 added step,stl and source 3d model file
2025-12-27 Updated README.md
    Updated README.md
2025-12-27 Added BOM
    Added BOM
2025-12-27 updated BOM again :(
2025-12-27 updated JOURNAL.md
    updated JOURNAL.md
2025-12-27 Small README.md update
    Small README.md update
2025-12-27 created code for Pico 2 of the wheel
2025-12-28 added the software for the pico 2 of the wheel base
2025-12-28 small changes to code
2025-12-28 Small update in README.md
    Small update in README.md
2025-12-28 Update README.md with small tips
    Update README.md with small tips
2026-01-05 added new images
2026-03-29 updated readme
    updated readme
2026-03-31 added pcb files (kicad 10)
2026-03-31 added software for BLDC MOTOR DRIVER PCB
